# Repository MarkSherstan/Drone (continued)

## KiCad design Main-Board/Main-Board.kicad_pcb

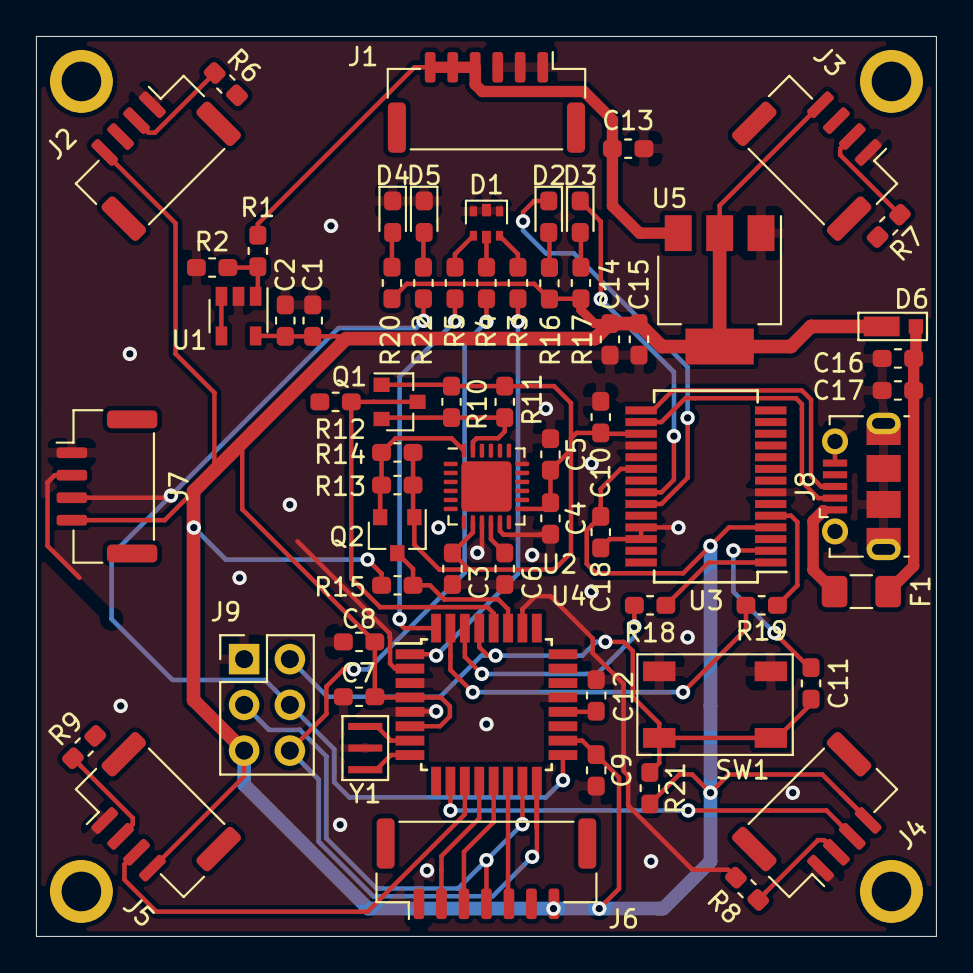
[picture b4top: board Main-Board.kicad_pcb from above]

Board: 2 copper layers, 50.0 x 50.0 mm, 69 parts (0 on the bottom side), 54 nets.

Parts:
C1, C7, C9, C15: 1uF 16V X7R 10%; C_0603_1608Metric_Pad1.05x0.95mm_HandSolder
C2, C5, C10, C11, C12, C17, C18: 0.1uF 16V X7R 10%; C_0603_1608Metric_Pad1.05x0.95mm_HandSolder
C3: 10nF 16V X7R 10%; C_0603_1608Metric_Pad1.05x0.95mm_HandSolder
C4: 2.2uF 16V X7R 10%; C_0603_1608Metric_Pad1.05x0.95mm_HandSolder
C6: 0.47uF 16V X7R 10%; C_0603_1608Metric_Pad1.05x0.95mm_HandSolder
C8, C16: 4.7uF 10V 20%; C_0603_1608Metric_Pad1.05x0.95mm_HandSolder
C13, C14: 10uF 25V 20%; C_0603_1608Metric_Pad1.05x0.95mm_HandSolder
D1: LED_RGB; RGB_LED
D2, D3: Orange 1.9V 20mA; LED_0603_1608Metric_Pad1.05x0.95mm_HandSolder
D4, D5: Green 2.2V 20mA; LED_0603_1608Metric_Pad1.05x0.95mm_HandSolder
D6: SS1P3L
F1: PTC 15V 500mA; Fuse_1206_3216Metric_Pad1.42x1.75mm_HandSolder
H1, H2, H3, H4: M2; MountingHole_2.2mm_M2_ISO7380_Pad
J1: Power_In; JST_GH_BM06B-GHS-TBT_1x06-1MP_P1.25mm_Vertical
J2: ESC_1; JST_GH_BM04B-GHS-TBT_1x04-1MP_P1.25mm_Vertical
J3: ESC_2; JST_GH_BM04B-GHS-TBT_1x04-1MP_P1.25mm_Vertical
J4: ESC_3; JST_GH_BM04B-GHS-TBT_1x04-1MP_P1.25mm_Vertical
J5: ESC_4; JST_GH_BM04B-GHS-TBT_1x04-1MP_P1.25mm_Vertical
J6: Receiver; JST_GH_BM07B-GHS-TBT_1x07-1MP_P1.25mm_Vertical
J7: Aux; JST_GH_BM04B-GHS-TBT_1x04-1MP_P1.25mm_Vertical
J8: USB_B_Micro; USB_Micro-B_Molex-105017-0001
J9: ICSP; PinHeader_2x03_P2.54mm_Vertical
Q1, Q2: BSS138; SOT-23
R1: 3.2 kohm 1%; R_0603_1608Metric_Pad1.05x0.95mm_HandSolder
R2: 2 kohm 1%; R_0603_1608Metric_Pad1.05x0.95mm_HandSolder
R3, R5: 100 ohm 5%; R_0603_1608Metric_Pad1.05x0.95mm_HandSolder
R4, R20: 150 ohm 5%; R_0603_1608Metric_Pad1.05x0.95mm_HandSolder
R6, R7, R8, R9: ?? ohm 5%; R_0603_1608Metric_Pad1.05x0.95mm_HandSolder
R10, R11, R12, R13, R14, R15: 10 kohm 5%; R_0603_1608Metric_Pad1.05x0.95mm_HandSolder
R16, R17, R22: 200 ohm 5%; R_0603_1608Metric_Pad1.05x0.95mm_HandSolder
R18, R19, R21: 1 kohm 5%; R_0603_1608Metric_Pad1.05x0.95mm_HandSolder
SW1: Reset; Switch
U1: MCP6001U; SOT-23-5
U2: ICM-20689; QFN-24-1EP_4x4mm_P0.5mm_EP2.8x2.8mm
U3: FT232RL; SSOP-28_5.3x10.2mm_P0.65mm
U4: ATmega328P-AU; TQFP-32_7x7mm_P0.8mm
U5: LM1117-5.0; SOT-223
Y1: 16 MHz; Resonator

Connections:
+3V3: C3.1, C4.1, C5.2, C10.1, Q1.1, Q2.1, R10.2, R11.2, R13.2, R14.2, U2.8, U2.13, U3.17
+5V: C1.2, C2.2, C7.2, C8.1, C9.1, C14.1, C15.1, C18.1, D6.1, J2.4, J3.4, J4.4, J5.4, J6.7, J7.4, J9.5, R12.2, R15.2, R16.2, R17.2, R20.2, R21.2, U1.5, U3.4, U3.20, U4.4, U4.6, U4.18, U5.2, U5.4
A0: U1.3, U1.4, U4.23
A1: R6.1, U4.24
A2: R7.1, U4.25
A3: R8.1, U4.26
A4_SDA: Q2.3, R15.1, U4.27
A5_SCL: Q1.3, R12.1, U4.28
A6: J7.2, U4.19
A7: R9.1, U4.22
Aux_Digital: J7.3, J9.4, R22.2, U4.17
B_RGB_LED: R3.1, U4.1
D2: R5.1, U4.32
D4: J2.3, U4.2
D5: J3.3, U4.9
D6: J4.3, U4.10
D7: J5.3, U4.11
D8: J6.2, U4.12
D9: J6.3, U4.13
D10: J6.5, U4.14
D11: J6.4, J9.3, U4.15
D12: J9.6, R4.1, U4.16
GND: C1.1, C2.1, C3.2, C4.2, C5.1, C6.2, C7.1, C8.2, C9.2, C10.2, C12.2, C13.2, C14.2, C15.2, C16.2, C17.2, C18.2, D1.2, D1.4, D1.6, D4.1, D5.1, J1.1, J1.2, J1.3, J2.1, J3.1, J4.1, J5.1, J6.1, J7.1, J8.5, J8.6, J9.1, R2.1, SW1.2, U1.2, U2.9, U2.11, U2.18, U3.7, U3.18, U3.21, U3.25, U3.26, U4.3, U4.5, U4.21, U5.1, Y1.2
IMU_SCL_LL: Q1.2, R10.1, R11.1, U2.23
IMU_SDA_LL: Q2.2, R13.1, R14.1, U2.24
unnamed: C6.1, U2.10
unnamed: C11.2, U3.2
unnamed: C12.1, U4.20
unnamed: D1.1, R3.2
unnamed: D1.3, R4.2
unnamed: D1.5, R5.2
unnamed: D2.1, U3.23
unnamed: D2.2, R16.1
unnamed: D3.1, U3.22
unnamed: D3.2, R17.1
unnamed: D4.2, R20.1
unnamed: D5.2, R22.1
unnamed: F1.1, J8.1
unnamed: J2.2, R6.2
unnamed: J3.2, R7.2
unnamed: J4.2, R8.2
unnamed: J5.2, R9.2
unnamed: J8.2, U3.16
unnamed: J8.3, U3.15
unnamed: R1.1, R2.2, U1.1
unnamed: R18.2, U4.30
unnamed: R19.2, U4.31
unnamed: U4.7, Y1.3
unnamed: U4.8, Y1.1
RESET: C11.1, J9.2, R21.1, SW1.1, U4.29
RX: R18.1, U3.1
TX: R19.1, U3.5
VBUS: C16.1, C17.1, D6.2, F1.2
VDD: C13.1, J1.4, J1.5, J1.6, R1.2, U5.3

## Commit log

2020-12-13 Initial commit of platformio files
2020-12-13 PCB initial commit
2020-12-13 ICM-20689 symbol created
2020-12-14 roughed out the imu schematic
2020-12-15 Initial test coupon and 3D print files
2020-12-15 Select ATMEGA328P as main processor, started to route.
2020-12-16 Gave everything their own sheet and made schematic for USB interface. USE 5 v logic for now
2020-12-17 Added in microcontroller voltage regulation
2020-12-18 Roughed the rest of the microcontroller schematic
2020-12-19 Added battery monitoring, some RGB LED, and general org
2020-12-19 Add RGB LED and added some additional pinout
2020-12-19 Filled out majority of microcontroller components and foot prints
2020-12-19 Added a few more footprints and component specifics. Created first net list
2020-12-20 Everything is in the schematic. Just need to review board then start the layout. Printed off hard copy
2020-12-20 Checked over page one, biggest question is what connectors to use
2020-12-20 Change to JST-GH connectors
2020-12-21 Review IMU, changed power in connector to 6 pos to prevent mis mating
2020-12-21 Initial glance over microcontroller schematic
2020-12-21 Reviewed MCU. Next have to generate BOM and route board
2020-12-21 Update .gitignore to allow .csv BOM
2020-12-21 Minor updates for components to reflect BOM
2020-12-21 BOM initial commit
2020-12-21 Switched from crystal to Resonator
2020-12-22 Routed IMU
2020-12-22 Shrunk board to approx 65 mm and layed out approx positions
2020-12-22 Dimensions 50 mm x 50 mm with 45 mm c-c holes. ESC connectors placed
2020-12-22 50% usb, ICSP, voltage monitoring, SDA/SCL, 48 tracks to go
2020-12-22 USB and voltage regulator routed, all components are now on the board
2020-12-22 more routing, back up before fixing some errors
2020-12-22 add attacheted lights to open ATMEGA ports (A4 cant be used again, dont mess with tx/rx) and removed 5th rc input. Add cap for USB
2020-12-23 New schematic time... Switching to ATmega32U4
2020-12-23 Deleted majority of unused components. Started schematic for new MCU
2020-12-24 Learned a lot about crystals
2020-12-24 Power Management and Selection roughed out
2020-12-24 USB interface
2020-12-30 Push before branch switch
2021-01-01 Mostly finished off the schematic, need to double check and label
2021-01-01 Updated pin mappings
2021-01-01 Main page and IMU reviewed and passed
2021-01-01 Microcontroller reviewed
2021-01-01 clean up refernces
2021-01-02 Create BOM and schematic
2021-01-02 Remove V0 PCB
2021-01-02 Clean up data sheets
2021-01-02 Group components
2021-01-02 Placed the crystal and IMU is mostly routed
2021-01-02 Power regulators routed
2021-01-02 everything placed
2021-01-02 Moved all components to the top of the board
2021-01-02 35 some traces left
2021-01-02 18 Traces left
2021-01-03 5 unrouted
2021-01-03 Silk screen and DRC then done. One Unrouted bug?'
2021-01-03 Board complete!
2021-01-03 Add gerbers
2021-01-03 Resaved schematic
2021-01-03 Initial schematic
2021-01-03 Schematic done
2021-01-03 board complete
2021-01-03 Make gerbers and PDF schematic
2021-01-04 Started schematic and board, created custom footprints
2021-01-05 all footprints complete
2021-01-05 fix + and - silk screen error
2021-01-05 Update notes
2021-01-07 Update file strcture before pull request
2021-01-10 Refresh the schematic and BOM
2021-01-10 add BOM
2021-01-10 Update part numbers and create BOM
2021-01-10 Update documentation
2021-01-10 Update file path
2021-01-10 Add .DS_Store
2021-01-10 Update board to reflect PCB (ATmega32U4)
2021-01-10 Initialize flight control with loop timer and RGB
2021-01-20 Start battery monitoring code and doxygen doc
2021-01-23 Set the full scale range and registers
2021-01-24 Finish IMU start up checks
2021-01-24 Change constructor to be extern
2021-01-24 Set up function read raw data and save in struct
2021-01-24 Add gyro calibration and process raw values
2021-01-24 Calculate attitude with comp filter
2021-01-24 Configure full scale range during initalization
2021-01-24 IMU configuration and gyro calibration complete
2021-01-24 Clean up variable names and added dt calc
2021-01-25 Monitor battery, create flash lights, update timer
2021-01-25 Add the class functions to the main script
2021-01-26 Remove extern and make status lights static
2021-01-31 Add PID initialization to main
2021-02-01 Add PID timer and tidy up main
2021-02-03 PID control initial...
2021-02-03 Each DOF has its own PID instance
2021-02-03 Add reset function and begin to contrains dynamics
2021-02-07 Add interupt service routine for RC
2021-02-07 Option to comiple and send over ICSP
2021-02-07 Move radio/receiver into flight controller class
2021-02-07 Clean up receiver variables with a struct
2021-02-07 Begin to process the raw receiver values
2021-02-09 Scale the receiver values
2021-02-11 Update build options and remove ICSP
2021-02-11 Initiate arm indicator LEDs on and set status LED
2021-02-11 Changed initalization of IMU class
2021-02-11 Updated main to work and better use status LEDs
2021-02-11 Tweak IMU connection and full scale range setting
2021-02-16 Change printing settings
2021-02-16 Add notes from PCB assembly
2021-02-28 Move rawRX struct from private to public for cal
2021-02-28 TX-Calibration initial commit
2022-02-21 Save TXRX debugging
2022-02-21 Formatting
2022-02-21 Tidy up comments
2022-02-21 Remove unused READMEs
2022-02-21 Data types and ensure 0 initial conditions
2022-02-21 Formatting and data types
2022-02-21 Tidy up comments and formatting
2022-02-21 Update structs
2022-02-21 Update main with class variable updates
2022-02-21 Prepare to split out receiver
2022-02-21 Split out receiver and flight control
2022-02-21 Clean up flight control
2022-02-21 Add wire / I2C to IMU class
2022-02-21 Change when the LED turns on
2022-02-21 Add interuppt stuffs
2022-02-21 Clean up function names
2022-02-21 Cleaning up main with changes from classes
2022-02-21 Change file and class name
2022-02-21 Add receiver back into main
2022-02-21 Remove config battery function (only use 3s)
2022-02-21 Update main with cleaned up Receiver class
2022-02-21 Begin receiver clean up
2022-02-21 Finish up tidy on receiver
2022-02-21 Reflect receiver updates
2022-02-23 TX Cal update
